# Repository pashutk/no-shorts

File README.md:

# USB-C Soldering Inspection Hat for Pi Pico

This repository contains a KiCad project for a Raspberry Pi Pico hat. The primary function of this device is to aid in the assessment of soldered USB-C connectors by identifying potential shorts. It offers a practical solution for those requiring a methodical approach to verify the integrity of their soldered USB-C connections.

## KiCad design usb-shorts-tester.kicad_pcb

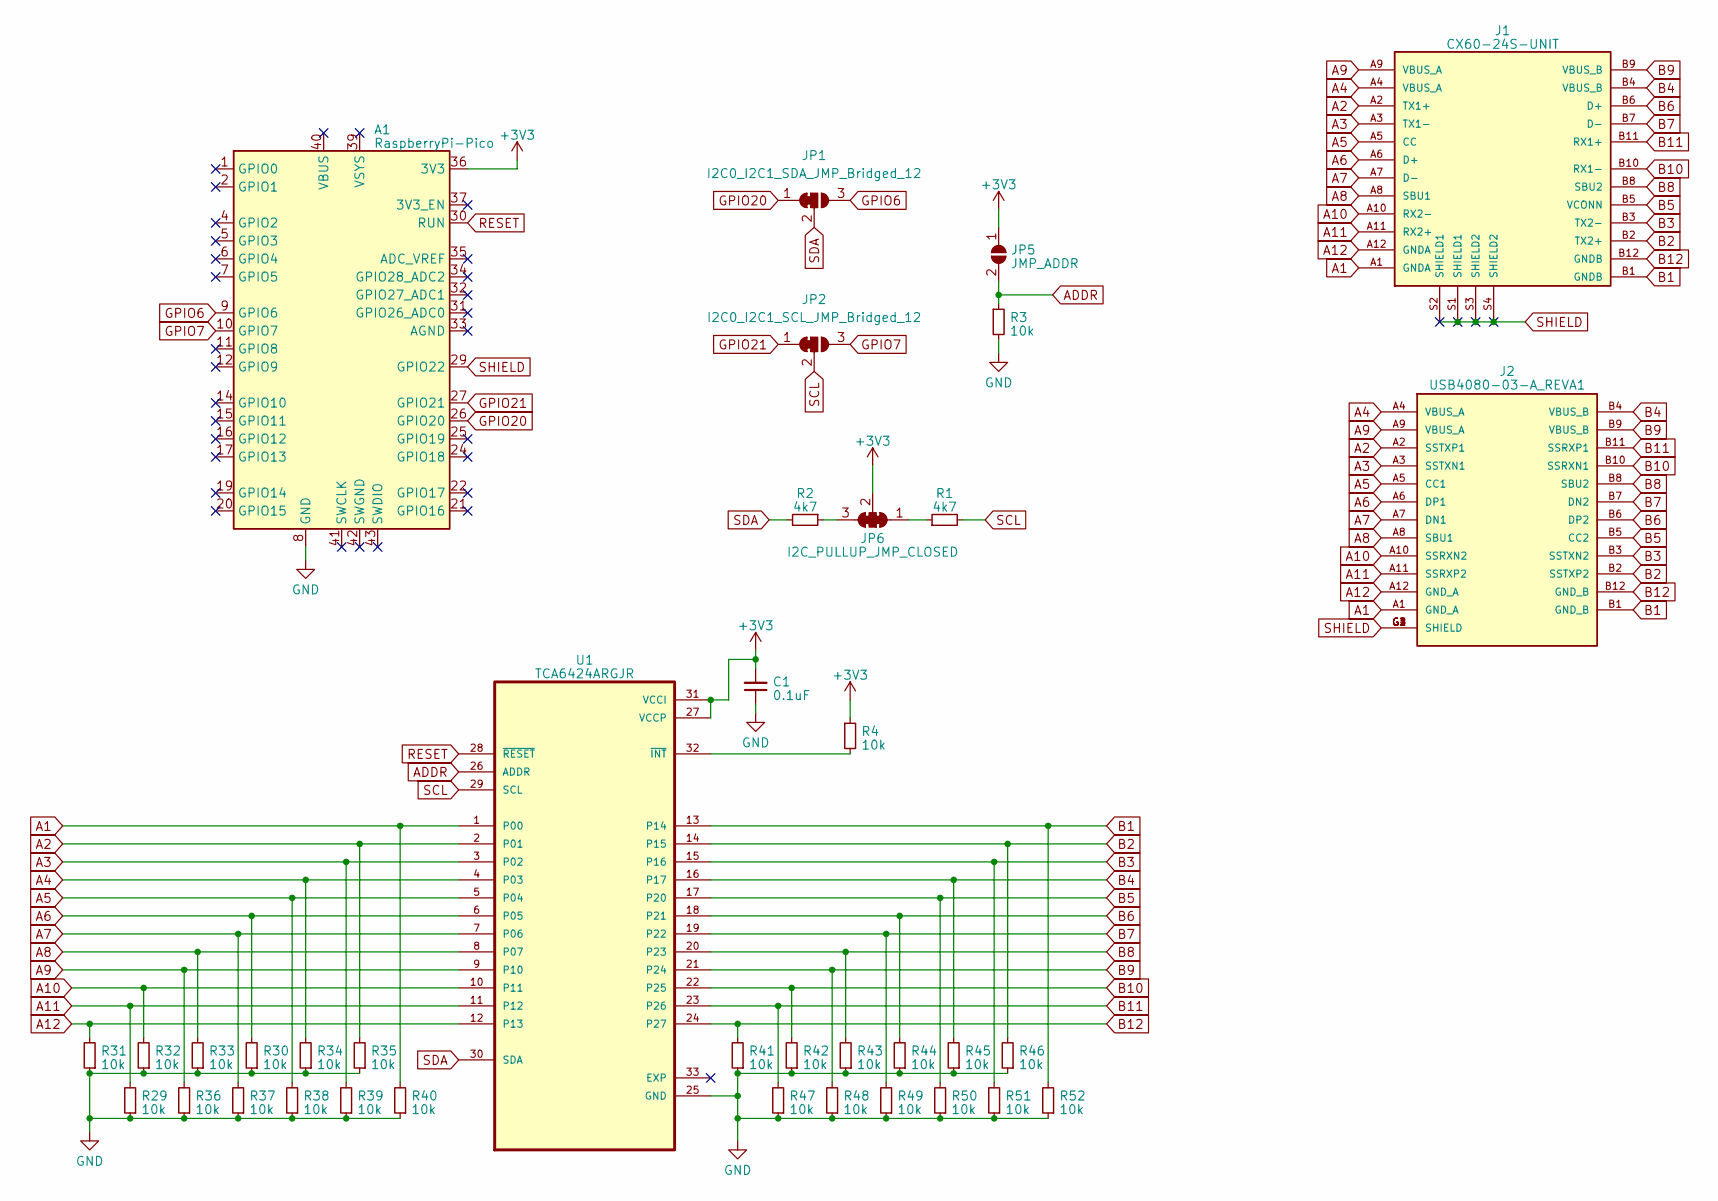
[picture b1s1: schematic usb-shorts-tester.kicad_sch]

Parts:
A1: RaspberryPi-Pico; Pi_Pico_AddOn
C1: 0.1uF; C_0603_1608Metric
J1: CX60-24S-UNIT; HIROSE_CX60-24S-UNIT; PARTREV 5
J2: USB4080-03-A_REVA1; GCT_USB4080-03-A_REVA1; PARTREV A1
JP1: I2C0_I2C1_SDA_JMP_Bridged_12; SolderJumper-3_P1.3mm_Bridged12_RoundedPad1.0x1.5mm
JP2: I2C0_I2C1_SCL_JMP_Bridged_12; SolderJumper-3_P1.3mm_Bridged12_RoundedPad1.0x1.5mm
JP5: JMP_ADDR; SolderJumper-2_P1.3mm_Open_RoundedPad1.0x1.5mm
JP6: I2C_PULLUP_JMP_CLOSED; SolderJumper-3_P1.3mm_Bridged12_RoundedPad1.0x1.5mm
R1, R2: 4k7; R_0603_1608Metric
R3, R4, R29, R30, R31, R32, R33, R34, R35, R36, R37, R38, R39, R40, R41, R42, R43, R44, R45, R46, R47, R48, R49, R50, R51, R52: 10k; R_0603_1608Metric
U1: TCA6424ARGJR; QFN50P500X500X60-33N

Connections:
+3V3: A1.36 (3V3), C1.2, JP5.1 (A), JP6.2 (C), R4.1, U1.27 (VCCP), U1.31 (VCCI)
A1: J1.A1 (GNDA), J2.A1 (GND_A), R40.2, U1.1 (P00)
A2: J1.A2 (TX1+), J2.A2 (SSTXP1), R35.2, U1.2 (P01)
A3: J1.A3 (TX1-), J2.A3 (SSTXN1), R39.2, U1.3 (P02)
A4: J1.A4 (VBUS_A), J2.A4 (VBUS_A), R34.2, U1.4 (P03)
A5: J1.A5 (CC), J2.A5 (CC1), R38.2, U1.5 (P04)
A6: J1.A6 (D+), J2.A6 (DP1), R30.2, U1.6 (P05)
A7: J1.A7 (D-), J2.A7 (DN1), R37.2, U1.7 (P06)
A8: J1.A8 (SBU1), J2.A8 (SBU1), R33.2, U1.8 (P07)
A9: J1.A9 (VBUS_A), J2.A9 (VBUS_A), R36.2, U1.9 (P10)
A10: J1.A10 (RX2-), J2.A10 (SSRXN2), R32.2, U1.10 (P11)
A11: J1.A11 (RX2+), J2.A11 (SSRXP2), R29.2, U1.11 (P12)
A12: J1.A12 (GNDA), J2.A12 (GND_A), R31.2, U1.12 (P13)
ADDR: JP5.2 (B), R3.1, U1.26 (ADDR)
B1: J1.B1 (GNDB), J2.B1 (GND_B), R52.2, U1.13 (P14)
B2: J1.B2 (TX2+), J2.B2 (SSTXP2), R46.2, U1.14 (P15)
B3: J1.B3 (TX2-), J2.B3 (SSTXN2), R51.2, U1.15 (P16)
B4: J1.B4 (VBUS_B), J2.B4 (VBUS_B), R45.2, U1.16 (P17)
B5: J1.B5 (VCONN), J2.B5 (CC2), R50.2, U1.17 (P20)
B6: J1.B6 (D+), J2.B6 (DP2), R44.2, U1.18 (P21)
B7: J1.B7 (D-), J2.B7 (DN2), R49.2, U1.19 (P22)
B8: J1.B8 (SBU2), J2.B8 (SBU2), R43.2, U1.20 (P23)
B9: J1.B9 (VBUS_B), J2.B9 (VBUS_B), R48.2, U1.21 (P24)
B10: J1.B10 (RX1-), J2.B10 (SSRXN1), R42.2, U1.22 (P25)
B11: J1.B11 (RX1+), J2.B11 (SSRXP1), R47.2, U1.23 (P26)
B12: J1.B12 (GNDB), J2.B12 (GND_B), R41.2, U1.24 (P27)
GND: A1.3 (GND), A1.8 (GND), A1.13 (GND), A1.18 (GND), A1.23 (GND), A1.28 (GND), A1.38 (GND), C1.1, R3.2, R29.1, R30.1, R31.1, R32.1, R33.1, R34.1, R35.1, R36.1, R37.1, R38.1, R39.1, R40.1, R41.1, R42.1, R43.1, R44.1, R45.1, R46.1, R47.1, R48.1, R49.1, R50.1, R51.1, R52.1, U1.25 (GND)
GPIO6: A1.9 (GPIO6), JP1.3 (B)
GPIO7: A1.10 (GPIO7), JP2.3 (B)
GPIO20: A1.26 (GPIO20), JP1.1 (A)
GPIO21: A1.27 (GPIO21), JP2.1 (A)
unnamed: JP6.1 (A), R1.1
unnamed: JP6.3 (B), R2.1
unnamed: R4.2, U1.32 (~INT)
RESET: A1.30 (RUN), U1.28 (~RESET)
SCL: JP2.2 (C), R1.2, U1.29 (SCL)
SDA: JP1.2 (C), R2.2, U1.30 (SDA)
SHIELD: A1.29 (GPIO22), J1.S1 (SHIELD1), J1.S2 (SHIELD1), J1.S3 (SHIELD2), J1.S4 (SHIELD2), J2.G1 (SHIELD), J2.G2 (SHIELD), J2.G3 (SHIELD), J2.G4 (SHIELD)

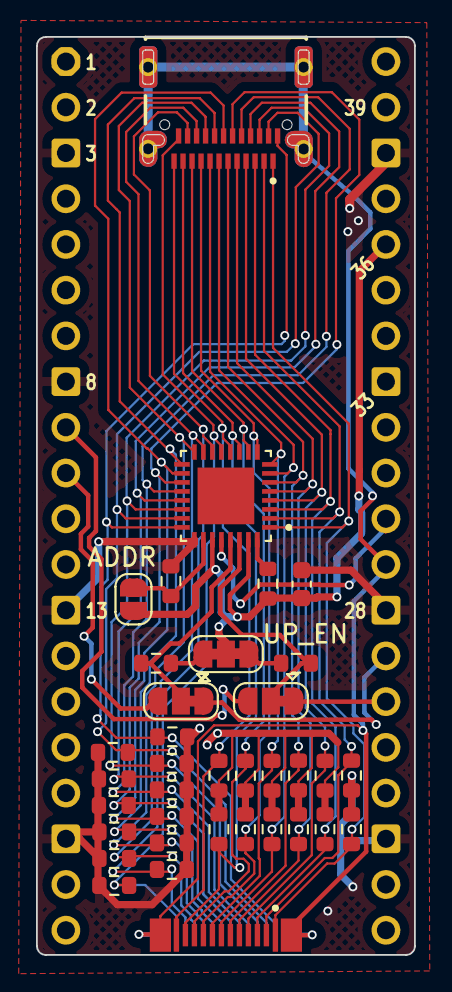
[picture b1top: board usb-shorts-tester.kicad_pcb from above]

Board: 2 copper layers, 21.0 x 51.0 mm, 37 parts (0 on the bottom side), 38 nets.

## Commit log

2023-08-27 Init
2023-08-28 Beta release
2023-09-03 Add usb shield probing
2023-09-23 Add pulldowns on all expander pins
